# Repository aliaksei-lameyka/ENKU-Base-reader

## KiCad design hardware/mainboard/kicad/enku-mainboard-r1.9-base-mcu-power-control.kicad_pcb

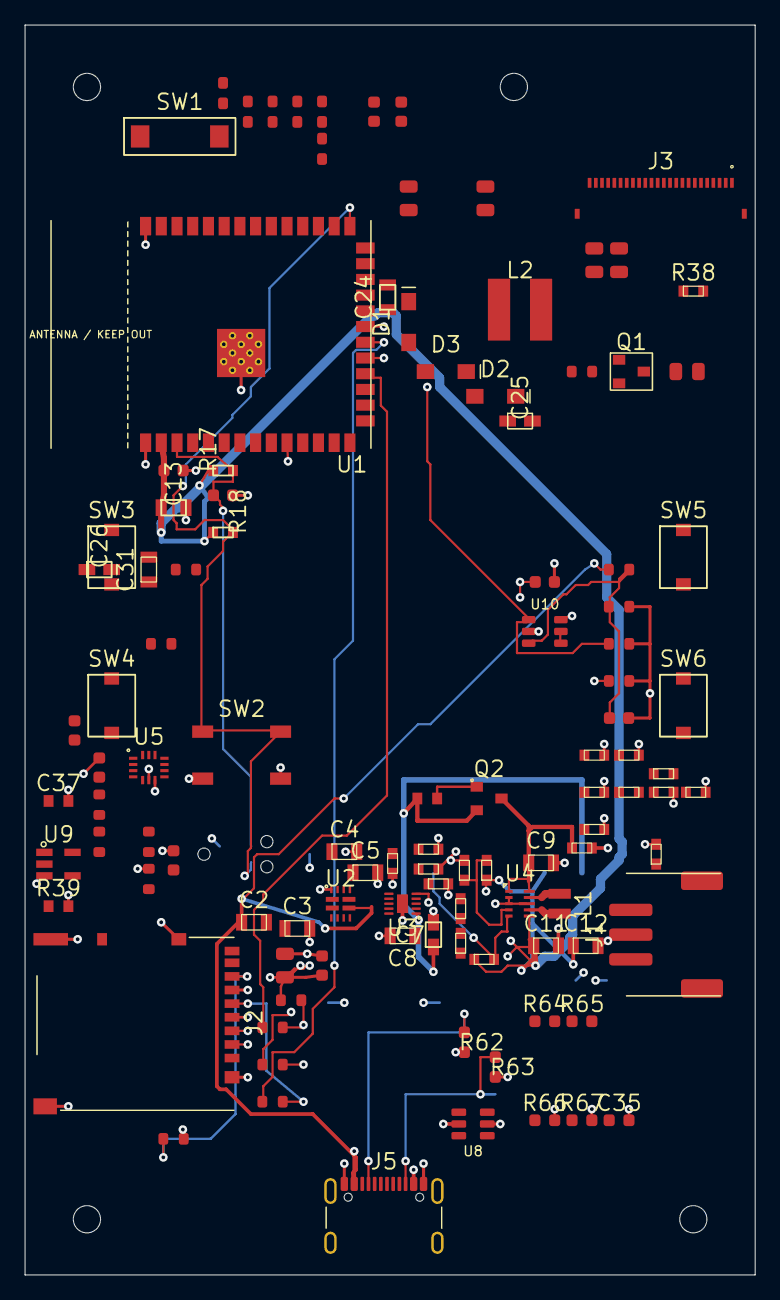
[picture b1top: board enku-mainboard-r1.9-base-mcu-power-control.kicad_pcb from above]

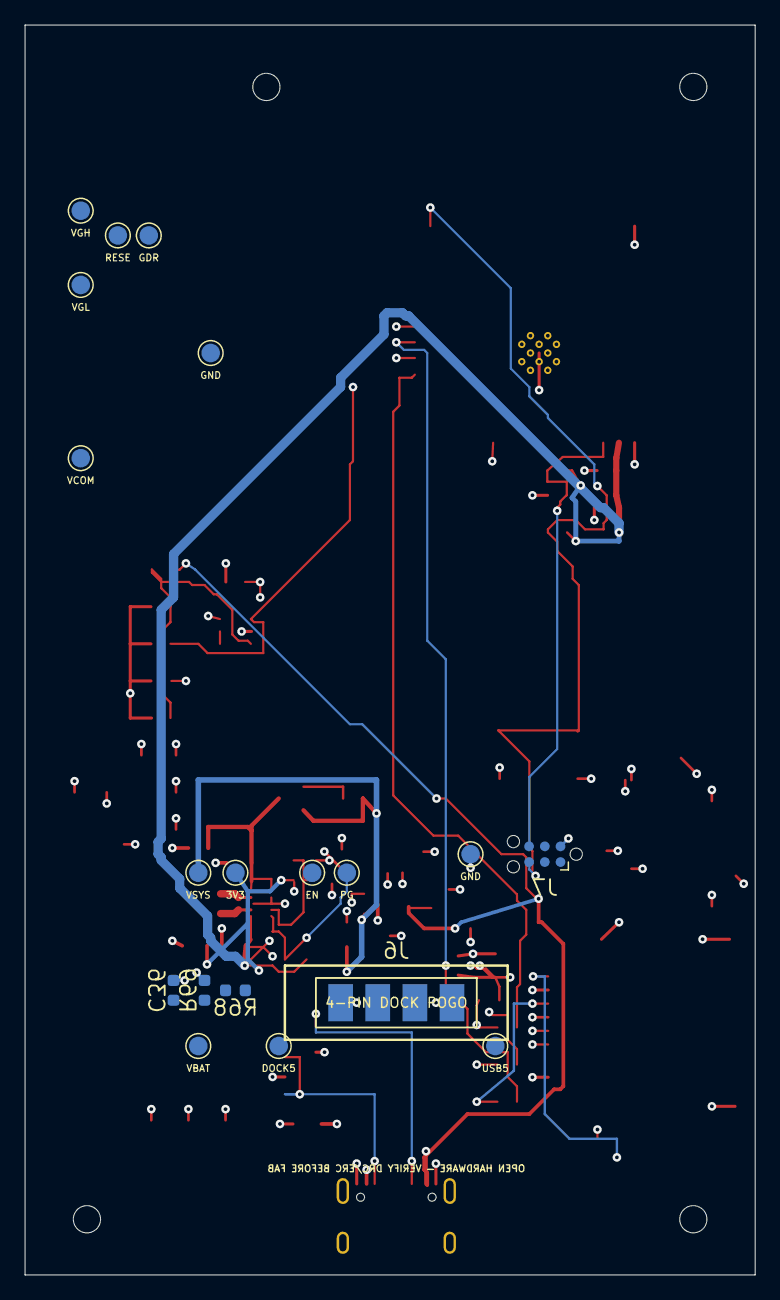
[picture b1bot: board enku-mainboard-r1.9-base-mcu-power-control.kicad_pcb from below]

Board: 4 copper layers, 59.0 x 101.0 mm, 132 parts (19 on the bottom side), 80 nets.

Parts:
C1, C10, C14, C17, C18, C19, C21: 100nF; C_0603_1608Metric
C2: 1uF 10V; C_0805_2012Metric
C3, C4, C9, C13, C16: 10uF 10V; C_0805_2012Metric
C5, C24, C25, C26, C27, C28, C29, C31: 4.7uF 25V; C_0805_2012Metric
C6: 100nF 25V; C_0603_1608Metric
C7: 10uF 25V; C_0805_2012Metric
C8: 4.7uF 10V; C_0805_2012Metric
C11, C12: 22uF 10V; C_0805_2012Metric
C15: 1uF; C_0603_1608Metric
C22, C23: 1uF 25V; C_0603_1608Metric
C30: 1uF 25V X7R; C_0805_2012Metric
C35: 4.7nF; C_0603_1608Metric
C36: 10nF; C_0603_1608Metric
C37, C38: 100nF 10V; C_0603_1608Metric
C39: 1nF C0G 10V; C_0603_1608Metric
D1, D2, D3: MBR0530; D_SOD-123
H1, H2, H3, H4: MountingHole_2.2mm_M2
J1: 1S LiPo + NTC; JST_PH_S3B-PH-SM4-TB_1x03-1MP_P2.00mm_Horizontal
J2: Hirose DM3AT-SF-PEJM5; MICROSD_DM3AT_ENKU
J3: FH34SRJ-24S-0.5SH(50); FH34SRJ-24S-0.5SH
J5: GCT USB4105-GF-A-120; USB_C_Receptacle_GCT_USB4105-xx-A_16P_TopMnt_Horizontal
J6: 4-pin pogo dock; DOCK_POGO_4
J7: Tag-Connect TC2030-IDC-NL; Tag-Connect_TC2030-IDC-NL_2x03_P1.27mm_Vertical
L1: 0.47uH DFE201612E-R47M=P2; Murata_DFE201612E
L2: 10uH TYS5040100M-10; TYS5040_5x5
Q1: IRLML6346TRPBF; SOT-23
Q2: AO3401A; SOT-23
R1, R40: 100k 1%; R_0603_1608Metric
R2, R3, R4, R5: 0R STRAP; R_0603_1608Metric
R6, R7, R19, R28, R29: 0R; R_0603_1608Metric
R8: 18k 1%; R_0603_1608Metric
R9: 1k 1%; R_0603_1608Metric
R10, R13, R16, R35, R36, R69, R72: 100k; R_0603_1608Metric
R11, R17, R18, R68: 10k; R_0603_1608Metric
R12: 10k DNP; R_0603_1608Metric
R14: 511k 1%; R_0603_1608Metric
R15: 91k 1%; R_0603_1608Metric
R20, R21, R22, R64, R65: 0R (22R tune); R_0603_1608Metric
R23: 47k; R_0603_1608Metric
R24, R25: 4.7k; R_0603_1608Metric
R26: 2M 1%; R_0603_1608Metric
R27: 680k 1%; R_0603_1608Metric
R30, R31, R32, R33, R34: 22R; R_0603_1608Metric
R37: 2.2R 1% 0805; R_0805_2012Metric
R38: 1M 1%; R_0603_1608Metric
R39, R66: 1M; R_0603_1608Metric
R62, R63: 5.1k 1%; R_0603_1608Metric
R67: 0R DNP; R_0603_1608Metric
R70: 26.7k 0.1% 25ppm; R_0603_1608Metric
R71: 10k 0.1% 25ppm; R_0603_1608Metric
R73: 3.3k 1%; R_0603_1608Metric
SW1: HARD POWER; HARD_POWER_SWITCH_PLACEMENT
SW2: BOOT / RECOVERY; SW_SPST_TL3342
SW3: BTN_L1; READING_BUTTON_PLACEMENT
SW4: BTN_L2; READING_BUTTON_PLACEMENT
SW5: BTN_R1; READING_BUTTON_PLACEMENT
SW6: BTN_R2; READING_BUTTON_PLACEMENT
TP1, TP14: GND; TestPoint_Pad_D1.5mm
TP2: VBUS_USB; TestPoint_Pad_D1.5mm
TP3: VBUS_DOCK; TestPoint_Pad_D1.5mm
TP4: VBAT; TestPoint_Pad_D1.5mm
TP5: VSYS; TestPoint_Pad_D1.5mm
TP6: 3V3_SYS; TestPoint_Pad_D1.5mm
TP7: SYS_EN; TestPoint_Pad_D1.5mm
TP8: REG_PG; TestPoint_Pad_D1.5mm
TP9: EPD_GDR; TestPoint_Pad_D1.5mm
TP10: EPD_RESE; TestPoint_Pad_D1.5mm
TP11: EPD_VGH; TestPoint_Pad_D1.5mm
TP12: EPD_VGL; TestPoint_Pad_D1.5mm
TP13: EPD_VCOM; TestPoint_Pad_D1.5mm
U1: ESP32-S3-WROOM-1-N16R8; ESP32-S3-WROOM-1
U2: TPS2121; TPS2121_RUX0012A
U3: BQ25185DLHR; BQ25185_DLH0010A
U4: TPS63802DLAR; TPS63802_DLA0010A
U5: BMI270; BMI270_Bosch_LGA14
U8: USBLC6-2SC6; USBLC6_2SC6_ST_SOT23_6L
U9: TMUX1101DBVR; SOT-23-5
U10: TLV3012BIDBVR; TLV3012B_DBV0006A

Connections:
3V3_SYS: C11.1, C12.1, C13.1, C14.1, C16.1, C17.1, C18.1, C19.1, C38.1, J2.4, J3.15, J7.1, R11.1, R12.1, R14.1, R16.1, R17.1, R18.1, R23.1, R24.1, R25.1, R28.1, R35.1, R36.1, R39.1, TP6.1, U1.2, U4.6, U5.5, U5.8, U5.12, U9.4, U10.6
BAT_ADC: C21.1, R26.2, R27.1, U1.39
BAT_ADC_SW: R26.1, U9.1
BAT_TS: J1.3, U3.6
BOOT: J7.5, R18.2, SW2.1, U1.27
BTN_L1: SW3.1, U1.4
BTN_L2: SW4.1, U1.5
BTN_R1: SW5.1, U1.6
BTN_R2: SW6.1, U1.7
CHG_CE_N: R10.1, U3.4
CHG_ILIM_VSET: R8.1, U3.7
CHG_ISET: R9.1, U3.8
CHG_STAT1: R11.2, U1.8, U3.9
CHG_STAT2: R12.2, U3.3
DOCK_DETECT: C36.1, R68.2, R69.1, U1.38
DOCK_DETECT_RAW: J6.3, R68.1
EPD_BS1: J3.8, R29.1
EPD_BUSY: J3.9, U1.25
EPD_CP_NEG: C25.2, D2.2, D3.1
EPD_CS: R32.1, U1.22
EPD_CS_PANEL: J3.12, R32.2, R35.2
EPD_DC: R31.1, U1.23
EPD_DC_PANEL: J3.11, R31.2
EPD_GDR: J3.2, Q1.1, R38.1, TP9.1
EPD_MOSI_PANEL: J3.14, R34.2
EPD_RESE: J3.3, Q1.2, R37.1, TP10.1
EPD_RST: R30.1, U1.24
EPD_RST_PANEL: J3.10, R30.2, R36.2
EPD_SCLK_PANEL: J3.13, R33.2
EPD_SW: C25.1, D1.2, L2.2, Q1.3
EPD_VCI: C22.1, C31.1, J3.16, L2.1, R28.2
EPD_VCOM: C30.1, J3.24, TP13.1
EPD_VDD: C23.1, J3.18
EPD_VGH: C24.1, D1.1, J3.21, TP11.1
EPD_VGL: C26.1, D3.2, J3.23, TP12.1
EPD_VSH1: C27.1, J3.20
EPD_VSH2: C28.1, J3.5
EPD_VSL: C29.1, J3.22
ESP_EN: C15.1, J7.6, R17.2, U1.3
GND: C1.2, C2.2, C3.2, C4.2, C5.2, C6.2, C7.2, C8.2, C9.2, C10.2, C11.2, C12.2, C13.2, C14.2, C15.2, C16.2, C17.2, C18.2, C19.2, C21.2, C22.2, C23.2, C24.2, C26.2, C27.2, C28.2, C29.2, C30.2, C31.2, C35.2, C36.2, C37.2, C38.2, C39.2, D2.1, J1.2, J2.6, J3.17, J3.S1, J3.S2, J5.A1, J5.A12, J5.B1, J5.B12, J6.1, J6.4, J7.2, R1.2, R3.2, R5.2, R6.2, R7.2, R8.2, R9.2, R10.2, R13.2, R15.2, R27.2, R29.2, R37.2, R38.2, R39.2, R62.2, R63.2, R66.2, R67.2, R69.2, R71.2, R72.2, R73.2, SW1.2, SW2.2, SW3.2, SW4.2, SW5.2, SW6.2, TP1.1, TP14.1, U1.1, U1.40, U1.41, U2.12, U3.5, U3.11, U4.2, U4.3, U4.8, U5.1, U5.6, U5.7, U8.2, U9.3, U10.2
I2C_SCL: R25.2, U1.17, U5.13
I2C_SDA: R24.2, U1.12, U5.14
IMU_INT1: U1.11, U5.4
MUX_CP2: R4.2, R5.1, U2.3
MUX_ILIM: R1.1, U2.10
MUX_OV1: R6.1, U2.5
MUX_OV2: R7.1, U2.4
MUX_PR1: R2.2, R3.1, U2.6
MUX_SS: C1.1, U2.11
PWR_GATE: Q2.1, R40.2, SW1.1
REG_FB: R14.2, R15.1, U4.4
REG_L1: L1.1, U4.9
REG_L2: L1.2, U4.7
REG_PG: R16.2, TP8.1, U4.5
SD_CS: R19.1, U1.18
SD_CS_CARD: J2.2, R19.2, R23.2
SD_MISO_CARD: J2.7, R22.1
SD_MOSI_CARD: J2.3, R20.2
SD_SCLK_CARD: J2.5, R21.2
SPI_MISO: R22.2, U1.21
SPI_MOSI: R20.1, R34.1, U1.19
SPI_SCLK: R21.1, R33.1, U1.20
SYS_EN: C9.1, C10.1, Q2.3, R13.1, TP7.1, U4.1, U4.10
UART_RX: J7.4, U1.36
UART_TX: J7.3, U1.37
USB_CC1: J5.A5, R62.1
USB_CC2: J5.B5, R63.1
USB_DM: R65.2, U1.13
USB_DM_CONN: J5.A7, J5.B7, R65.1, U8.3, U8.4
USB_DP: R64.2, U1.14
USB_DP_CONN: J5.A6, J5.B6, R64.1, U8.1, U8.6
USB_SHIELD: C35.1, J5.S, R66.1, R67.1
USB_VBUS_DIV: C39.1, R70.2, R71.1, U10.3
USB_VBUS_REF: U10.4, U10.5
USB_VBUS_VALID: R72.1, U1.10, U10.1
VBAT: C8.1, C37.1, J1.1, TP4.1, U3.2, U9.2, U9.5
VBUS_DOCK: C3.1, J6.2, R4.1, TP3.1, U2.2
VBUS_EXT: C4.1, C5.1, C6.1, U2.1, U2.8, U3.10
VBUS_USB: C2.1, J5.A4, J5.A9, J5.B4, J5.B9, R2.1, R70.1, R73.1, TP2.1, U2.7, U8.5
VSYS: C7.1, Q2.2, R40.1, TP5.1, U3.1

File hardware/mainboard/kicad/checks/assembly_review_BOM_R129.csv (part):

Reference,Value,Manufacturer,MPN,Assembly,Footprint,Side,BoardX_mm,BoardY_mm,NativeCPL_X_mm,NativeCPL_Y_mm,Rotation_deg,MPN_field_status
C10,100nF,Yageo,CC0603KRX7R9BB104,FIT,ENKU:C_CC0603_YAGEO_REFLOW_TRANSFER,front,63.0,86.5,63.0,-86.5,0.0,EXPLICIT
C11,22uF 10V,Yageo,CC0805MKX5R6BB226,FIT,ENKU:C_CC0805_YAGEO_REFLOW_TRANSFER,front,60.1,94.4,60.1,-94.4,0.0,EXPLICIT
C12,22uF 10V,Yageo,CC0805MKX5R6BB226,FIT,ENKU:C_CC0805_YAGEO_REFLOW_TRANSFER,front,63.125,94.4,63.125,-94.4,0.0,EXPLICIT
C13,10uF 10V,Yageo,CC0805KKX5R6BB106,FIT,ENKU:C_CC0805_YAGEO_REFLOW_TRANSFER,front,30.0,59.0,30.0,-59.0,0.0,EXPLICIT
C14,100nF,Yageo,CC0603KRX7R9BB104,FIT,ENKU:C_CC0603_YAGEO_REFLOW_TRANSFER,front,30.0,56.0,30.0,-56.0,0.0,EXPLICIT
C15,1uF,Yageo,CC0603KRX7R8BB105,FIT,ENKU:C_CC0603_YAGEO_REFLOW_TRANSFER,front,34.0,58.0,34.0,-58.0,0.0,EXPLICIT
C16,10uF 10V,Yageo,CC0805KKX5R6BB106,FIT,ENKU:C_CC0805_YAGEO_REFLOW_TRANSFER,front,39.0,96.0,39.0,-96.0,90.0,EXPLICIT
C17,100nF,Yageo,CC0603KRX7R9BB104,FIT,ENKU:C_CC0603_YAGEO_REFLOW_TRANSFER,front,42.0,96.0,42.0,-96.0,90.0,EXPLICIT
C18,100nF,Yageo,CC0603KRX7R9BB104,FIT,ENKU:C_CC0603_YAGEO_REFLOW_TRANSFER,front,22.0,77.4,22.0,-77.4,90.0,EXPLICIT
C19,100nF,Yageo,CC0603KRX7R9BB104,FIT,ENKU:C_CC0603_YAGEO_REFLOW_TRANSFER,front,24.0,80.0,24.0,-80.0,90.0,EXPLICIT
C2,1uF 10V,Yageo,CC0805KKX7R6BB105,FIT,ENKU:C_CC0805_YAGEO_REFLOW_TRANSFER,front,36.5,91.85,36.5,-91.85,0.0,EXPLICIT
C21,100nF,Yageo,CC0603KRX7R9BB104,FIT,ENKU:C_CC0603_YAGEO_REFLOW_TRANSFER,front,30.0,87.5,30.0,-87.5,90.0,EXPLICIT
C22,1uF 25V,Yageo,CC0603KRX7R8BB105,FIT,ENKU:C_CC0603_YAGEO_REFLOW_TRANSFER,front,46.2,27.0,46.2,-27.0,90.0,EXPLICIT
C23,1uF 25V,Yageo,CC0603KRX7R8BB105,FIT,ENKU:C_CC0603_YAGEO_REFLOW_TRANSFER,front,48.4,27.0,48.4,-27.0,90.0,EXPLICIT
C24,4.7uF 25V,Yageo,CC0805KKX7R8BB475,FIT,ENKU:C_CC0805_YAGEO_REFLOW_TRANSFER,front,47.3,42.0,47.3,-42.0,90.0,EXPLICIT
C25,4.7uF 25V,Yageo,CC0805KKX7R8BB475,FIT,ENKU:C_CC0805_YAGEO_REFLOW_TRANSFER,front,58.0,52.0,58.0,-52.0,0.0,EXPLICIT
C26,4.7uF 25V,Yageo,CC0805KKX7R8BB475,FIT,ENKU:C_CC0805_YAGEO_REFLOW_TRANSFER,front,52.5,45.5,52.5,-45.5,90.0,EXPLICIT
C27,4.7uF 25V,Yageo,CC0805KKX7R8BB475,FIT,ENKU:C_CC0805_YAGEO_REFLOW_TRANSFER,front,49.0,34.0,49.0,-34.0,90.0,EXPLICIT
C28,4.7uF 25V,Yageo,CC0805KKX7R8BB475,FIT,ENKU:C_CC0805_YAGEO_REFLOW_TRANSFER,front,73.12,28.5,73.12,-28.5,90.0,EXPLICIT
C29,4.7uF 25V,Yageo,CC0805KKX7R8BB475,FIT,ENKU:C_CC0805_YAGEO_REFLOW_TRANSFER,front,64.0,39.0,64.0,-39.0,90.0,EXPLICIT
C30,1uF 25V X7R,Yageo,CC0805KKX7R8BB105,FIT,ENKU:C_CC0805_YAGEO_REFLOW_TRANSFER,front,66.0,39.0,66.0,-39.0,90.0,EXPLICIT
C31,4.7uF 25V,Yageo,CC0805KKX7R8BB475,FIT,ENKU:C_CC0805_YAGEO_REFLOW_TRANSFER,front,53.0,43.0,53.0,-43.0,180.0,EXPLICIT
C35,4.7nF,Yageo,CC0603KRX7R9BB472,FIT,ENKU:C_CC0603_YAGEO_REFLOW_TRANSFER,front,66.0,108.5,66.0,-108.5,0.0,EXPLICIT
C37,100nF 10V,Yageo,CC0603KRX7R9BB104,FIT,ENKU:C_CC0603_YAGEO_REFLOW_TRANSFER,front,38.5,67.0,38.5,-67.0,0.0,EXPLICIT
C38,100nF 10V,Yageo,CC0603KRX7R9BB104,FIT,ENKU:C_CC0603_YAGEO_REFLOW_TRANSFER,front,60.0,65.0,60.0,-65.0,0.0,EXPLICIT
C39,1nF C0G 10V,Yageo,CC0603JRNPO9BN102,FIT,ENKU:C_CC0603_YAGEO_REFLOW_TRANSFER,front,66.0,76.0,66.0,-76.0,0.0,EXPLICIT
C4,1uF 25V,Yageo,CC0805KKX7R8BB105,FIT,ENKU:C_CC0805_YAGEO_REFLOW_TRANSFER,front,43.8,86.8,43.8,-86.8,0.0,EXPLICIT
C5,4.7uF 25V,Yageo,CC0805KKX7R8BB475,FIT,ENKU:C_CC0805_YAGEO_REFLOW_TRANSFER,front,45.5,88.5,45.5,-88.5,0.0,EXPLICIT
C6,100nF 25V,Yageo,CC0603KRX7R9BB104,FIT,ENKU:C_CC0603_YAGEO_REFLOW_TRANSFER,front,45.5,93.0,45.5,-93.0,0.0,EXPLICIT
C7,10uF 25V,Yageo,CC0805KKX5R8BB106,FIT,ENKU:C_CC0805_YAGEO_REFLOW_TRANSFER,front,51.6,93.5,51.6,-93.5,90.0,EXPLICIT
C8,4.7uF 10V,Yageo,CC0805KKX5R6BB475,FIT,ENKU:C_CC0805_YAGEO_REFLOW_TRANSFER,front,48.5,93.6,48.5,-93.6,180.0,EXPLICIT
C9,10uF 10V,Yageo,CC0805KKX5R6BB106,FIT,ENKU:C_CC0805_YAGEO_REFLOW_TRANSFER,front,59.7,87.7,59.7,-87.7,0.0,EXPLICIT
D1,MBR0530T1G,onsemi,MBR0530T1G,FIT,ENKU:MBR0530T1G_ONSEMI_CASE425H,front,49.25,44.0,49.25,-44.0,-90.0,EXPLICIT
D2,MBR0530T1G,onsemi,MBR0530T1G,FIT,ENKU:MBR0530T1G_ONSEMI_CASE425H,front,56.0,50.0,56.0,-50.0,180.0,EXPLICIT
D3,MBR0530T1G,onsemi,MBR0530T1G,FIT,ENKU:MBR0530T1G_ONSEMI_CASE425H,front,52.0,48.0,52.0,-48.0,180.0,EXPLICIT
H1,,,,BARE_PCB,ENKU:MOUNT_HOLE_D2_2_BOARD_ONLY,front,29.0,22.5,,,0.0,NOT_AN_ASSEMBLED_PART
H2,,,,BARE_PCB,ENKU:MOUNT_HOLE_D2_2_BOARD_ONLY,front,57.5,25.0,,,0.0,NOT_AN_ASSEMBLED_PART
H3,,,,BARE_PCB,ENKU:MOUNT_HOLE_D2_2_BOARD_ONLY,front,23.0,116.5,,,0.0,NOT_AN_ASSEMBLED_PART
H4,,,,BARE_PCB,ENKU:MOUNT_HOLE_D2_2_BOARD_ONLY,front,72.0,116.5,,,0.0,NOT_AN_ASSEMBLED_PART
J1,1S LiPo + NTC,,,FIT,ENKU:JST_PH_S3B-PH-SM4-TB_1x03-1MP_P2.00mm_Horizontal,front,69.8,93.5,69.8,-93.5,90.0,FIELD_FREEZE_PENDING
J2,Hirose DM3AT-SF-PEJM5,,,FIT,ENKU:MICROSD_DM3AT_ENKU,front,27.0,100.7,27.0,-100.7,-90.0,FIELD_FREEZE_PENDING
J3,FH34SRJ-24S-0.5SH(50),Hirose,FH34SRJ-24S-0.5SH(50),FIT,ENKU:FH34SRJ-24S-0.5SH,front,69.27,34.0,69.27,-34.0,0.0,EXPLICIT
J5,GCT USB4105-GF-A-120,,,FIT,ENKU:USB4105_EXISTING_LANDS_SHIELD_S,front,47.0,117.325,47.0,-117.325,0.0,FIELD_FREEZE_PENDING
J7,Tag-Connect TC2030-IDC-NL,,,BARE_PCB,ENKU:TC2030_NL_CONTACTS_PIN1,back,35.0,87.0,,,0.0,NOT_AN_ASSEMBLED_PART
L1,0.47uH DFE201612E-R47M=P2,,,FIT,ENKU:Murata_DFE201612E,front,61.2,91.0,61.2,-91.0,-90.0,FIELD_FREEZE_PENDING
L2,47uH TYS5040470M-10,,,FIT,ENKU:TYS5040_5x5,front,58.0,43.0,58.0,-43.0,0.0,FIELD_FREEZE_PENDING
Q1,IRLML6346TRPBF,,,FIT,ENKU:IRLML6346_INFINEON_MICRO3,front,67.0,48.0,67.0,-48.0,0.0,FIELD_FREEZE_PENDING
Q2,AO3401A,,,FIT,ENKU:AO3401A_AOS_SOT23,front,55.5,82.5,55.5,-82.5,0.0,FIELD_FREEZE_PENDING
R10,100k,Yageo,RC0603FR-07100KL,FIT,ENKU:R_RC0603_YAGEO_REFLOW,front,51.8,89.4,51.8,-89.4,0.0,EXPLICIT
R11,10k,Yageo,RC0603FR-0710KL,FIT,ENKU:R_RC0603_YAGEO_REFLOW,front,53.2,91.4,53.2,-91.4,90.0,EXPLICIT
R12,10k DNP,Yageo,RC0603FR-0710KL,DNP,ENKU:R_RC0603_YAGEO_REFLOW,front,53.3,94.2,,,90.0,EXPLICIT
R13,100k,Yageo,RC0603FR-07100KL,FIT,ENKU:R_RC0603_YAGEO_REFLOW,front,69.0,85.3,69.0,-85.3,90.0,EXPLICIT
R14,511k 1%,Yageo,RC0603FR-07511KL,FIT,ENKU:R_RC0603_YAGEO_REFLOW,front,55.3,88.3,55.3,-88.3,90.0,EXPLICIT
R15,91k 1%,Yageo,RC0603FR-0791KL,FIT,ENKU:R_RC0603_YAGEO_REFLOW,front,53.9,88.3,53.9,-88.3,90.0,EXPLICIT
R16,100k,Yageo,RC0603FR-07100KL,FIT,ENKU:R_RC0603_YAGEO_REFLOW,front,55.45,95.5,55.45,-95.5,0.0,EXPLICIT
R17,10k,Yageo,RC0603FR-0710KL,FIT,ENKU:R_RC0603_YAGEO_REFLOW,front,34.0,56.0,34.0,-56.0,0.0,EXPLICIT
R18,10k,Yageo,RC0603FR-0710KL,FIT,ENKU:R_RC0603_YAGEO_REFLOW,front,34.0,61.0,34.0,-61.0,0.0,EXPLICIT
R19,0R,Yageo,RC0603JR-070RL,FIT,ENKU:R_RC0603_YAGEO_REFLOW,front,38.0,101.0,38.0,-101.0,0.0,EXPLICIT
R20,0R (22R tune),Yageo,RC0603JR-070RL,FIT,ENKU:R_RC0603_YAGEO_REFLOW,front,38.0,104.0,38.0,-104.0,0.0,EXPLICIT
R21,0R (22R tune),Yageo,RC0603JR-070RL,FIT,ENKU:R_RC0603_YAGEO_REFLOW,front,38.0,107.0,38.0,-107.0,0.0,EXPLICIT
R22,0R (22R tune),Yageo,RC0603JR-070RL,FIT,ENKU:R_RC0603_YAGEO_REFLOW,front,30.0,110.0,30.0,-110.0,0.0,EXPLICIT
R23,47k,Yageo,RC0603FR-0747KL,FIT,ENKU:R_RC0603_YAGEO_REFLOW,front,39.5,98.8,39.5,-98.8,0.0,EXPLICIT
R24,4.7k,Yageo,RC0603FR-074K7L,FIT,ENKU:R_RC0603_YAGEO_REFLOW,front,26.0,76.5,26.0,-76.5,90.0,EXPLICIT
R25,4.7k,Yageo,RC0603FR-074K7L,FIT,ENKU:R_RC0603_YAGEO_REFLOW,front,26.0,73.0,26.0,-73.0,90.0,EXPLICIT
R26,2M 1%,Yageo,RC0603FR-072ML,FIT,ENKU:R_RC0603_YAGEO_REFLOW,front,28.0,86.0,28.0,-86.0,90.0,EXPLICIT
R27,680k 1%,Yageo,RC0603FR-07680KL,FIT,ENKU:R_RC0603_YAGEO_REFLOW,front,28.0,89.0,28.0,-89.0,90.0,EXPLICIT
R28,0R,Yageo,RC0603JR-070RL,FIT,ENKU:R_RC0603_YAGEO_REFLOW,front,63.0,48.0,63.0,-48.0,0.0,EXPLICIT
R29,0R,Yageo,RC0603JR-070RL,FIT,ENKU:R_RC0603_YAGEO_REFLOW,front,42.0,30.0,42.0,-30.0,90.0,EXPLICIT
R30,22R,Yageo,RC0603FR-0722RL,FIT,ENKU:R_RC0603_YAGEO_REFLOW,front,42.0,27.0,42.0,-27.0,90.0,EXPLICIT
R31,22R,Yageo,RC0603FR-0722RL,FIT,ENKU:R_RC0603_YAGEO_REFLOW,front,40.0,27.0,40.0,-27.0,90.0,EXPLICIT
R32,22R,Yageo,RC0603FR-0722RL,FIT,ENKU:R_RC0603_YAGEO_REFLOW,front,38.0,27.0,38.0,-27.0,90.0,EXPLICIT
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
